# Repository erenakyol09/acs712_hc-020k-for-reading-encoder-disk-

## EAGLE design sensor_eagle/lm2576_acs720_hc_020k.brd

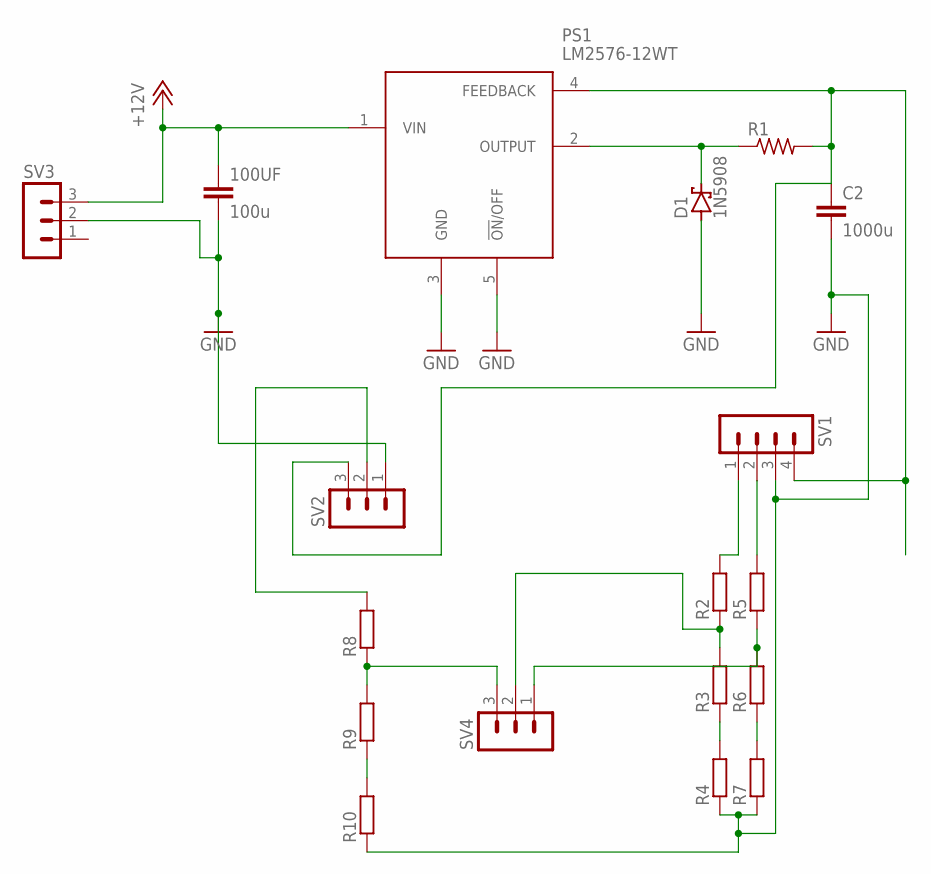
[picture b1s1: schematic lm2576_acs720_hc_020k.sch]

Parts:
100UF: 100u; C5B5
C2: 1000u; C5B5
D1: 1N5908; C4111-15
PS1: LM2576-12WT; TO170P470X1016X1900-5P
R1: R-US_VTA55; VTA55
R2, R3, R4, R5, R6, R7, R8, R9, R10: R-EU_0207/12; 0207/12
SV1: MA04-1
SV2, SV3, SV4: MA03-1

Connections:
+5V: C2.1, PS1.4 (FEEDBACK), R1.2, SV1.4, SV2.3
+12V: 100UF.1, PS1.1 (VIN), SV3.3
GND: 100UF.2, C2.2, D1.A, PS1.3 (GND), PS1.5 (!ON!/OFF), R4.1, R7.1, R10.1, SV1.3, SV2.1, SV3.2
unnamed: R8.1, R9.2, SV4.3
unnamed: D1.C, PS1.2 (OUTPUT), R1.1
unnamed: R5.1, R6.2, SV4.1
unnamed: R3.1, R4.2
unnamed: R9.1, R10.2
unnamed: R6.1, R7.2
unnamed: R8.2, SV2.2
unnamed: R2.1, R3.2, SV4.2
unnamed: R2.2, SV1.1
unnamed: R5.2, SV1.2

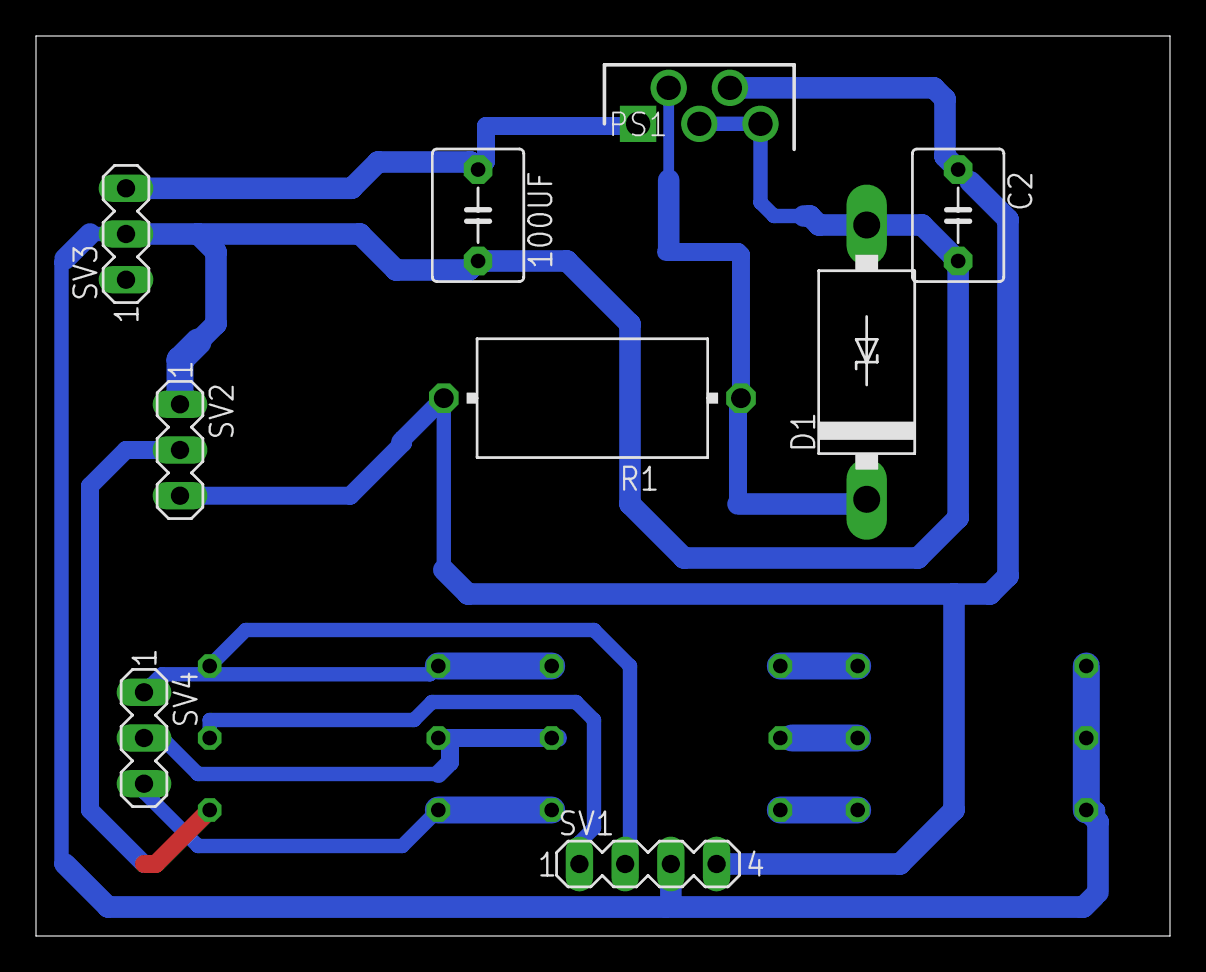
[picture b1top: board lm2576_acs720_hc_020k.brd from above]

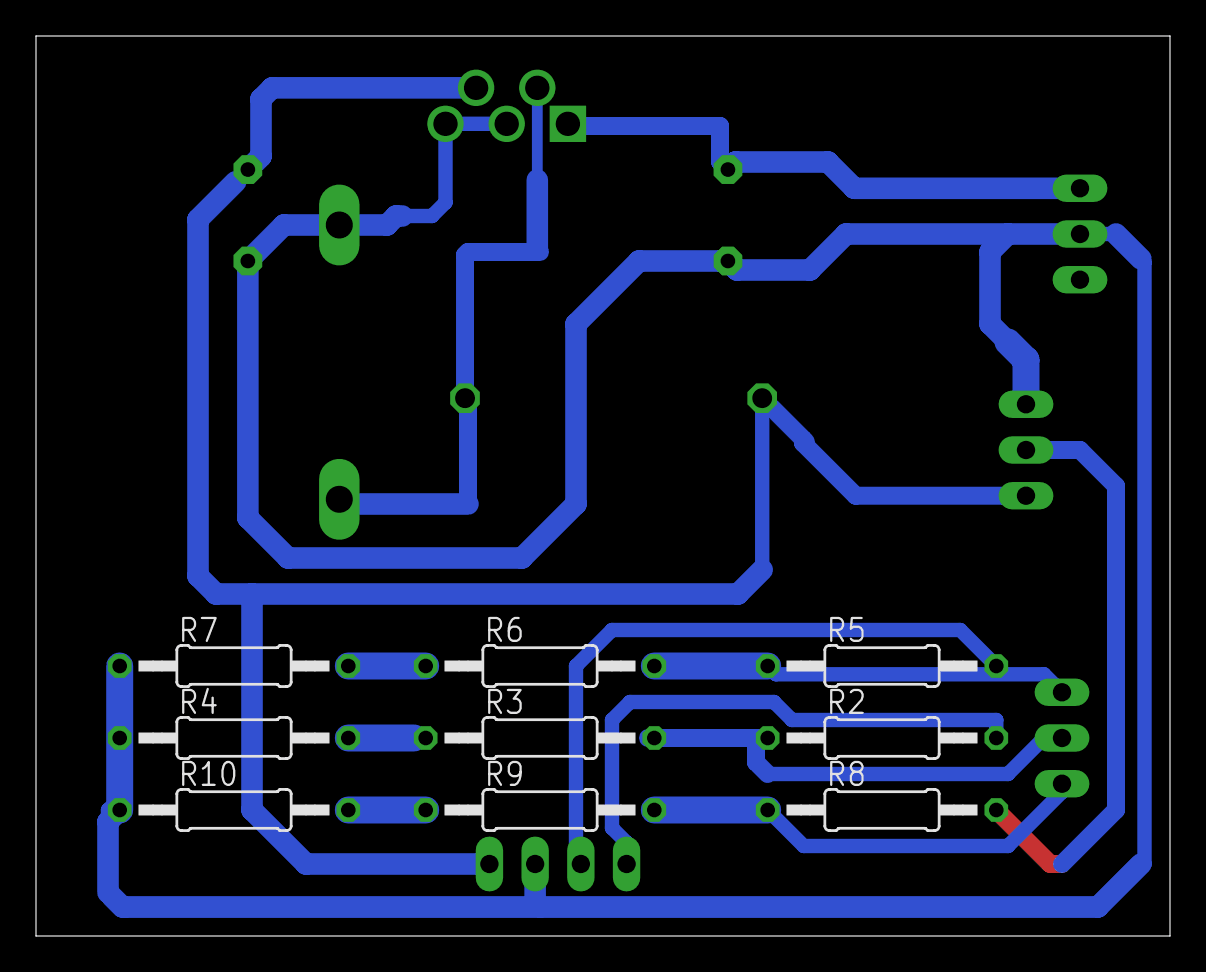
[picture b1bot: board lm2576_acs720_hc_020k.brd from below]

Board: 2 copper layers, 63.0 x 50.0 mm, 18 parts (9 on the bottom side), 13 nets.

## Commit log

2020-07-20 sensors
